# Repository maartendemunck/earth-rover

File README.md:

# Earth Rover

This repository contains the documentation, designs, circuit diagrams, PCB
layouts and firmware of my earth rover (RC Volvo C202) project.

## Electronics

The `electronics` subdirectory contains the circuit diagrams and PCB layouts for
the different components, created with KiCad:

- `human-machine-interface`: main human machine interface (HMI) PCB
- `joystick`: joystick breakout boards for the human machine interface
- `vehicle-control-unit`: main vehicle control unit (VCU) PCB
- `position-encoder`: position encoder for the main driveshaft
- `panel`: panel for fabrication of the PCBs
- `kicad-libraries`: libraries with schematic symbols and component footprints

## Software

The `software/remote-control` subdirectory contains the firmware for a manual
remote control:

- `human-machine-interface`: PlatformIO project for the Teensy 3.2-based human
   machine interface
- `human-machine-interface-display`: Nextion project for the Nextion Enhanced
   NX4827K043 HMI touch display
- `vehicle-control-unit`: PlatformIO project for the Teensy 3.2-based vehicle
   control unit

## License

The earth rover hardware, software and accompanying documentation are released
under the [3-Clause BSD License](https://opensource.org/license/bsd-3-clause/).

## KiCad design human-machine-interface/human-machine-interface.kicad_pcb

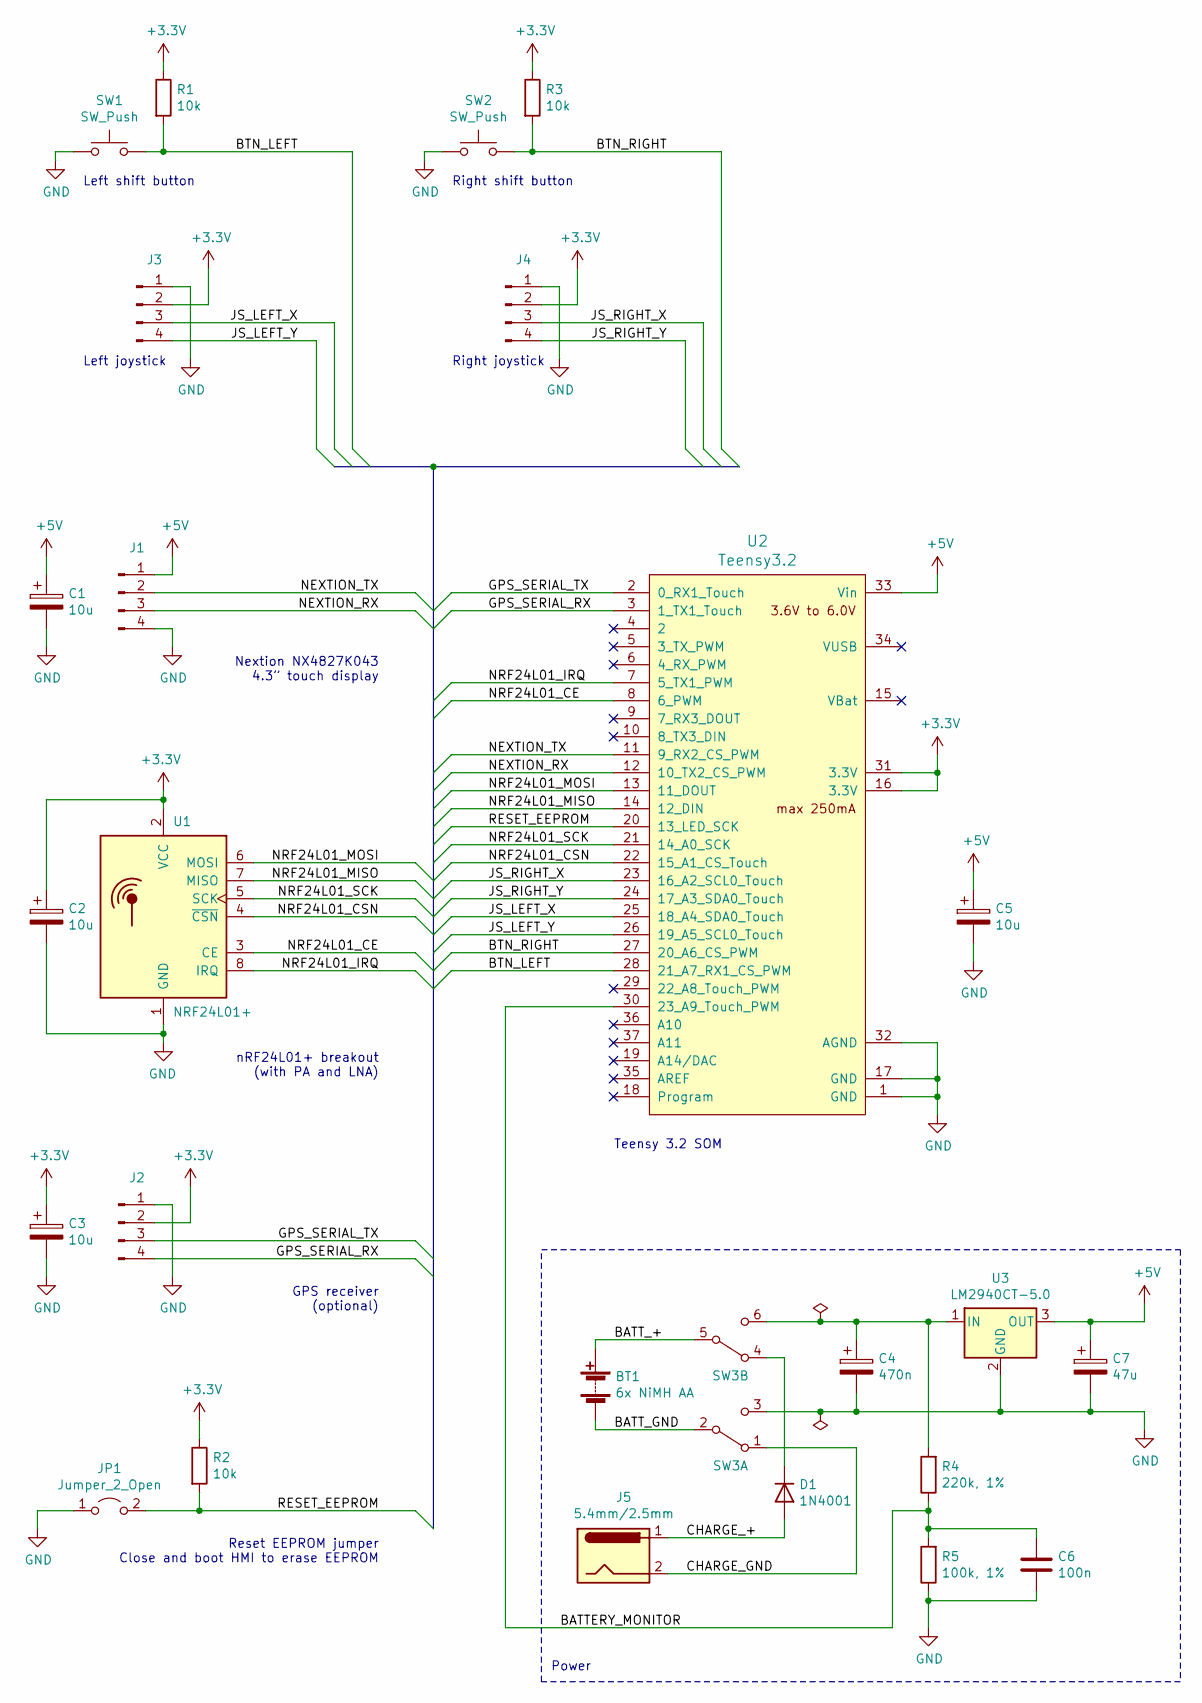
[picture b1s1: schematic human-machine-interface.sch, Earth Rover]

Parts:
BT1: 6x NiMH AA; PinHeader_1x02_P2.54mm_Vertical
C1, C2, C3, C5: 10u; CP_Radial_D5.0mm_P2.50mm
C4: 470n; C_Rect_L10.0mm_W5.0mm_P5.00mm_P7.50mm
C6: 100n; C_Rect_L10.0mm_W5.0mm_P5.00mm_P7.50mm
C7: 47u; CP_Radial_D5.0mm_P2.50mm
D1: 1N4001; D_DO-41_SOD81_P10.16mm_Horizontal
J1, J2, J3, J4: Conn_01x04_Male; PinHeader_1x04_P2.54mm_Vertical
J5: 5.4mm/2.5mm; PinHeader_1x02_P2.54mm_Vertical
JP1: Jumper_2_Open; PinHeader_1x02_P2.54mm_Vertical
R1, R2, R3: 10k; R_Axial_DIN0207_L6.3mm_D2.5mm_P10.16mm_Horizontal
R4: 220k, 1%; R_Axial_DIN0207_L6.3mm_D2.5mm_P10.16mm_Horizontal
R5: 100k, 1%; R_Axial_DIN0207_L6.3mm_D2.5mm_P10.16mm_Horizontal
SW1, SW2: SW_Push; PinHeader_1x02_P2.54mm_Vertical
SW3: SW_DPDT_x2; PinHeader_2x03_P2.54mm_Vertical_Switch_DPDT
U1: NRF24L01+; nRF24L01_Breakout_LargerHoles
U2: Teensy3.2; Teensy_3.2
U3: LM2940CT-5.0; TO-220-3_Vertical

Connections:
+3V3: C2.1, C3.1, J2.2, J3.2, J4.2, R1.1, R2.1, R3.1, U1.2 (VCC), U2.16 (3.3V), U2.31 (3.3V)
+5V: C1.1, C5.1, C7.1, J1.1, U2.33 (Vin), U3.3 (OUT)
/BATTERY_MONITOR: C6.1, R4.1, R5.2, U2.30 (23_A9_Touch_PWM)
/BATT_+: BT1.1 (+), SW3.5 (B)
/BATT_GND: BT1.2 (-), SW3.2 (B)
/BTN_LEFT: R1.2, SW1.2, U2.28 (21_A7_RX1_CS_PWM)
/BTN_RIGHT: R3.2, SW2.2, U2.27 (20_A6_CS_PWM)
/CHARGE_+: D1.2 (A), J5.1
/CHARGE_GND: J5.2, SW3.1 (A)
/GPS_SERIAL_RX: J2.4, U2.3 (1_TX1_Touch)
/GPS_SERIAL_TX: J2.3, U2.2 (0_RX1_Touch)
/JS_LEFT_X: J3.3, U2.25 (18_A4_SDA0_Touch)
/JS_LEFT_Y: J3.4, U2.26 (19_A5_SCL0_Touch)
/JS_RIGHT_X: J4.3, U2.23 (16_A2_SCL0_Touch)
/JS_RIGHT_Y: J4.4, U2.24 (17_A3_SDA0_Touch)
/NEXTION_RX: J1.3, U2.12 (10_TX2_CS_PWM)
/NEXTION_TX: J1.2, U2.11 (9_RX2_CS_PWM)
/NRF24L01_CE: U1.3 (CE), U2.8 (6_PWM)
/NRF24L01_CSN: U1.4 (~CSN), U2.22 (15_A1_CS_Touch)
/NRF24L01_IRQ: U1.8 (IRQ), U2.7 (5_TX1_PWM)
/NRF24L01_MISO: U1.7 (MISO), U2.14 (12_DIN)
/NRF24L01_MOSI: U1.6 (MOSI), U2.13 (11_DOUT)
/NRF24L01_SCK: U1.5 (SCK), U2.21 (14_A0_SCK)
/RESET_EEPROM: JP1.2 (B), R2.2, U2.20 (13_LED_SCK)
GND: C1.2, C2.2, C3.2, C4.2, C5.2, C6.2, C7.2, J1.4, J2.1, J3.1, J4.1, JP1.1 (A), R5.1, SW1.1, SW2.1, SW3.3 (C), U1.1 (GND), U2.1 (GND), U2.17 (GND), U2.32 (AGND), U3.2 (GND)
unnamed: C4.1, R4.2, SW3.6 (C), U3.1 (IN)
unnamed: D1.1 (K), SW3.4 (A)

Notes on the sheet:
GPS receiver (optional)
Right joystick
Reset EEPROM jumper Close and boot HMI to erase EEPROM
Power
nRF24L01+ breakout (with PA and LNA)
Left shift button
Left joystick
Right shift button
Nextion NX4827K043 4.3” touch display
Teensy 3.2 SOM

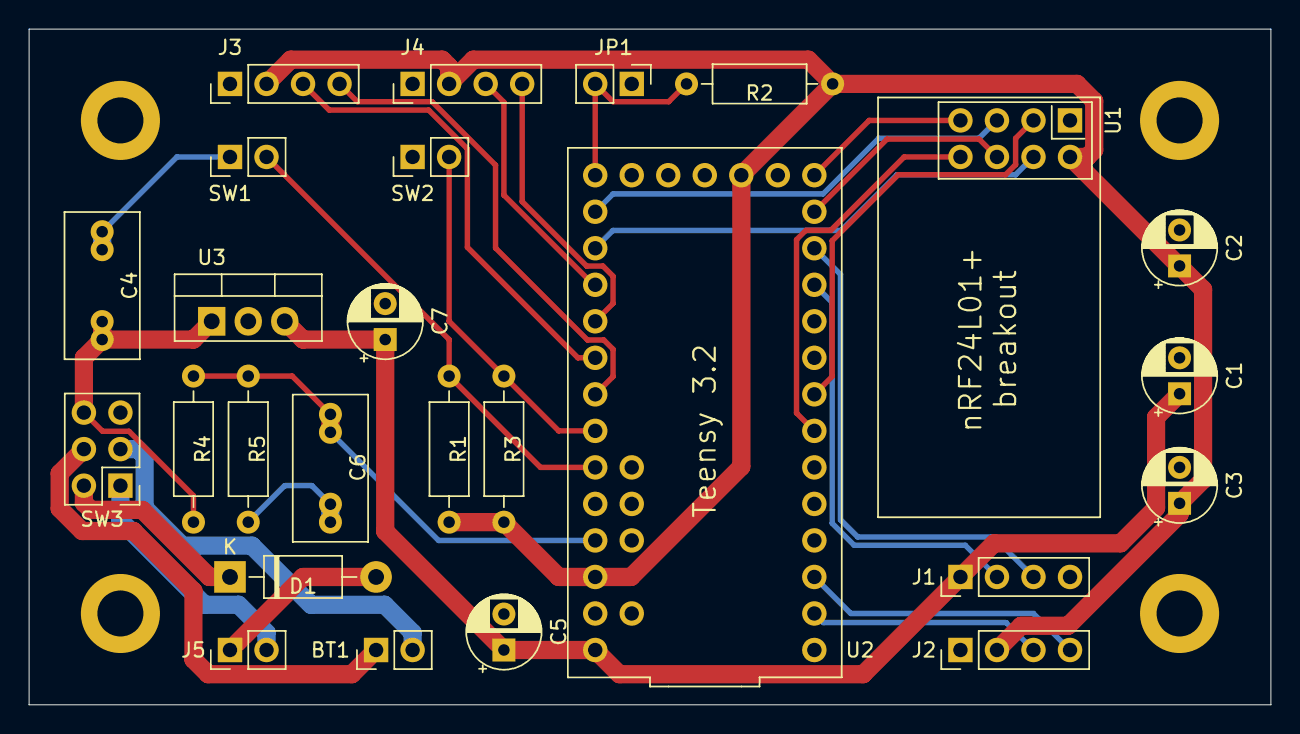
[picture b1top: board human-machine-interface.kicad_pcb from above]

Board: 2 copper layers, 86.4 x 47.0 mm, 26 parts (0 on the bottom side), 27 nets.

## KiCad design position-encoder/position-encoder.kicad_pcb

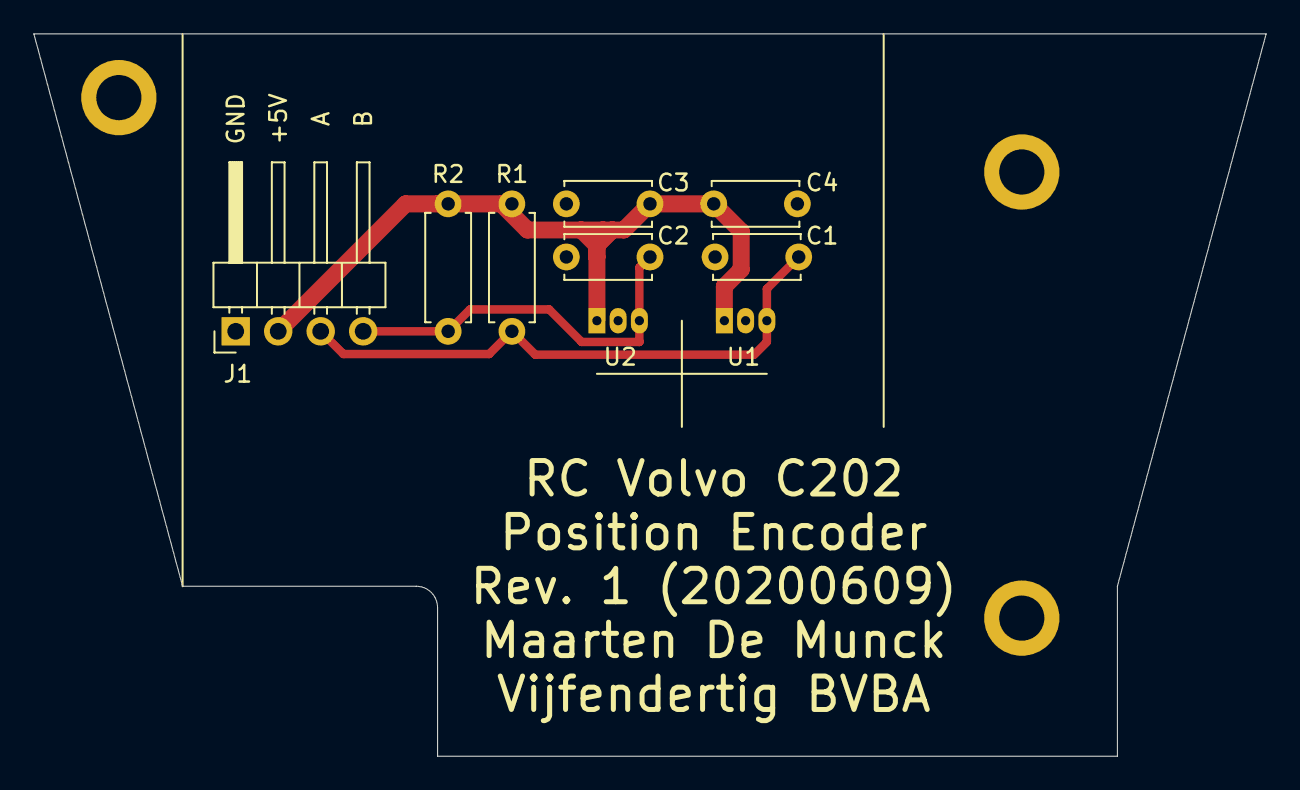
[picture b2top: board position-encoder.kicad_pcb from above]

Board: 2 copper layers, 73.7 x 43.2 mm, 9 parts (0 on the bottom side), 4 nets.

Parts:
C1, C2, C3, C4: 4.7nF; C_Disc_D5.0mm_W2.5mm_P5.00mm
J1: Conn_01x04_Male; PinHeader_1x04_P2.54mm_Horizontal
R1, R2: 10kΩ; R_Axial_DIN0207_L6.3mm_D2.5mm_P7.62mm_Horizontal
U1, U2: TLE4905L; PG-SSO-3-2_W2.54mm_Horizontal_Down

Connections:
+5V: C3.1, C4.1, J1.2, R1.1, R2.1, U1.1, U2.1
GND: C1.2, C2.2, C3.2, C4.2, J1.1, U1.2, U2.2
unnamed: C1.1, J1.3, R1.2, U1.3
unnamed: C2.1, J1.4, R2.2, U2.3

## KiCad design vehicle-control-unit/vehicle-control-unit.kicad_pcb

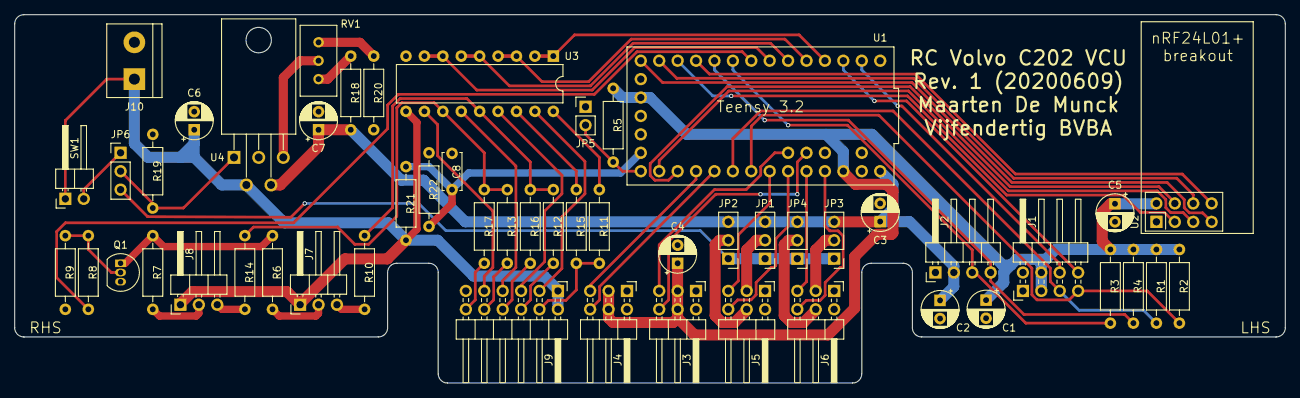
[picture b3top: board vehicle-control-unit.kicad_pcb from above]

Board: 2 copper layers, 175.3 x 50.8 mm, 53 parts (0 on the bottom side), 60 nets.

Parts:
C1, C2, C3, C4, C5, C6: 10u; CP_Radial_D5.0mm_P2.50mm
C7: 22u; CP_Radial_D5.0mm_P2.50mm
C8: 100n; C_Disc_D5.0mm_W2.5mm_P5.00mm
J1: Conn_02x04_Male_UnitPerRow; PinHeader_2x04_P2.54mm_Horizontal
J2: Conn_01x04_Male; PinHeader_1x04_P2.54mm_Horizontal
J3, J4, J5, J6: Conn_02x03_Male; PinHeader_2x03_P2.54mm_Horizontal
J7, J8: Conn_01x03_Male; PinHeader_1x03_P2.54mm_Horizontal
J9: Conn_02x06_Male_UnitPerRow; PinHeader_2x06_P2.54mm_Horizontal
J10: Connector:Screw_Terminal_01x02; TerminalBlock_bornier-2_P5.08mm
JP1, JP2, JP3, JP4, JP6: Jumper_3_Bridged12; PinHeader_1x03_P2.54mm_Vertical
JP5: Jumper_2_Open; PinHeader_1x02_P2.54mm_Vertical
Q1: BC517; TO-92_Inline
R1, R2, R3, R4, R5, R8, R19: 10k; R_Axial_DIN0207_L6.3mm_D2.5mm_P10.16mm_Horizontal
R6, R7: 10E; R_Axial_DIN0207_L6.3mm_D2.5mm_P10.16mm_Horizontal
R9: 100k; R_Axial_DIN0207_L6.3mm_D2.5mm_P10.16mm_Horizontal
R10, R14, R16, R17: 330E; R_Axial_DIN0207_L6.3mm_D2.5mm_P10.16mm_Horizontal
R11: 470E; R_Axial_DIN0207_L6.3mm_D2.5mm_P10.16mm_Horizontal
R12, R13: 180E; R_Axial_DIN0207_L6.3mm_D2.5mm_P10.16mm_Horizontal
R15: 82E; R_Axial_DIN0207_L6.3mm_D2.5mm_P10.16mm_Horizontal
R18: 820E; R_Axial_DIN0207_L6.3mm_D2.5mm_P10.16mm_Horizontal
R20: 240E; R_Axial_DIN0207_L6.3mm_D2.5mm_P10.16mm_Horizontal
R21: 270k, 1%; R_Axial_DIN0207_L6.3mm_D2.5mm_P10.16mm_Horizontal
R22: 100k, 1%; R_Axial_DIN0207_L6.3mm_D2.5mm_P10.16mm_Horizontal
RV1: 100E; Potentiometer_Bourns_3296W_Vertical
SW1: SW_SPST; PinHeader_1x02_P2.54mm_Horizontal
U1: Teensy3.2; Teensy_3.2
U2: NRF24L01+ breakout; nRF24L01_Breakout_LargerHoles
U3: ULN2803A; DIP-18_W7.62mm
U4: MIC29502WT; TO-220-5_P3.4x3.8mm_StaggerEven_Lead7.13mm_TabDown

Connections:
+3V3: C1.1, C4.1, C5.1, J1.3, J1.4, J3.3, J3.4, J4.3, J4.4, R1.1, R2.1, R3.1, R4.1, R5.1, U1.16, U1.31, U2.2
+5V: C2.1, C3.1, C7.1, J2.2, JP1.3, JP2.3, JP3.3, JP4.3, R18.1, U1.33, U4.4
+BATT: C6.1, J7.1, J8.1, J9.1, J9.2, J10.1, R21.1, SW1.1, U3.10, U4.2
/BATTERY_MONITOR: C8.1, R21.2, R22.1, U1.19
/BEC: JP1.1, JP2.1, JP3.1, JP4.1, JP6.3
/ENCODER_A: J2.3, R3.2, U1.9
/ENCODER_B: J2.4, R4.2, U1.10
/GEARBOX: J6.5, U1.29
/GPS_SERIAL_RX: J1.8, U1.3
/GPS_SERIAL_TX: J1.6, U1.2
/HEADLAMPS: R8.2, U1.8
/IMU_I2C_SCL: J1.7, R2.2, U1.26
/IMU_I2C_SDA: J1.5, R1.2, U1.25
/LEFT_TURN_SIGNALS: U1.6, U3.5, U3.6
/NRF24L01_CE: U1.12, U2.3
/NRF24L01_CSN: U1.22, U2.4
/NRF24L01_IRQ: U1.11, U2.8
/NRF24L01_MISO: U1.14, U2.7
/NRF24L01_MOSI: U1.13, U2.6
/NRF24L01_SCK: U1.21, U2.5
/POSITION_LAMPS: U1.4, U3.1, U3.2
/RESET_EEPROM: JP5.2, R5.2, U1.20
/RIGHT_TURN_SIGNALS: U1.7, U3.7, U3.8
/SENSOR_1: J3.6, U1.36
/SENSOR_2: J3.5, U1.37
/SENSOR_3: J4.6, U1.24
/SENSOR_4: J4.5, U1.23
/STEERING: J5.5, U1.27
/STOP_LAMPS: U1.5, U3.3, U3.4
/THROTTLE: J5.6, U1.28
/WINCH: J6.6, U1.30
GND: C1.2, C2.2, C3.2, C4.2, C5.2, C6.2, C7.2, C8.2, J1.1, J1.2, J2.1, J3.1, J3.2, J4.1, J4.2, J5.1, J5.2, J6.1, J6.2, J9.11, J10.2, JP5.1, Q1.3, R9.2, R19.2, R20.2, R22.2, U1.1, U1.17, U1.32, U2.1, U3.9, U4.3
unnamed: J5.3, JP1.2
unnamed: J5.4, JP2.2
unnamed: J6.3, JP3.2
unnamed: J6.4, JP4.2
unnamed: J7.2, R6.1
unnamed: J7.3, R10.1
unnamed: J8.2, R7.1
unnamed: J8.3, R14.1
unnamed: J9.3, U3.17
unnamed: J9.4, R11.1, R15.1
unnamed: J9.5, U3.15
unnamed: J9.6, R12.1
unnamed: J9.7, U3.13
unnamed: J9.8, R16.1
unnamed: J9.9, U3.11
unnamed: J9.10, R13.1
unnamed: J9.12, R17.1
unnamed: JP6.1, SW1.2
unnamed: JP6.2, R19.1, U4.1
unnamed: Q1.1, R6.2, R7.2
unnamed: Q1.2, R8.1, R9.1
unnamed: R10.2, R12.2, R16.2, U3.14
unnamed: R11.2, U3.18
unnamed: R13.2, R14.2, R17.2, U3.12
unnamed: R15.2, U3.16
unnamed: R18.2, RV1.1
unnamed: R20.1, RV1.3
unnamed: RV1.2, U4.5

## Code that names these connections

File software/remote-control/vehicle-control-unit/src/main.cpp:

// Copyright 2019-2023 Vijfendertig BV.
//
// This file is part of the Earth Rover project, which is licensed under the 3-Clause BSD License.
// See the file LICENSE.md or go to https://opensource.org/license/bsd-3-clause/ for full license
// details.

#include <Arduino.h>
#include <i2c_t3.h>

#include "adafruit-bno055-wrapper.hpp"
#include "lighting.hpp"
#include "neogps-wrapper.hpp"
#include "position-encoder.hpp"
#include "powertrain.hpp"
#include "radio-configuration.hpp"
#include "steering-servo.hpp"
#include "vcu-communicator.hpp"
#include "vcu.hpp"

// #define SERIAL_DEBUG

constexpr uint8_t spi_sck_pin = 14u;  // Use the default SCK pin 13 as status LED.

auto makeVcu() {
    constexpr uint16_t config_eeprom_block_offset = 0u;
    constexpr uint16_t config_eeprom_block_size = 2048u;
    constexpr uint8_t steering_servo_pin = 20u;
    constexpr uint8_t esc_pin = 21u;
    constexpr uint8_t gearbox_servo_pin = 22u;
    constexpr uint8_t head_lamp_pin = 6u;
    constexpr uint8_t tail_lamp_pin = 2u;
    constexpr uint8_t stop_lamp_pin = 3u;
    constexpr uint8_t turn_signal_left_pin = 4u;
    constexpr uint8_t turn_signal_right_pin = 5u;
    constexpr uint8_t hall_sensor_a_pin = 7u;
    constexpr uint8_t hall_sensor_b_pin = 8u;
    constexpr uint16_t pulses_per_km = 23000u;
    constexpr auto &imu_i2c = Wire;
    constexpr uint8_t imu_i2c_scl_pin = 19u;
    constexpr uint8_t imu_i2c_sda_pin = 18u;
    constexpr auto &gps_serial = Serial1;
    constexpr uint8_t gps_serial_rx_pin = 0u;
    constexpr uint8_t gps_serial_tx_pin = 1u;
    earth_rover::SteeringServo steering_servo{steering_servo_pin};
    earth_rover::Powertrain powertrain{esc_pin, gearbox_servo_pin};
    earth_rover::Lighting lighting{head_lamp_pin, tail_lamp_pin, stop_lamp_pin,
                                   turn_signal_right_pin, turn_signal_left_pin};
    earth_rover::PositionEncoder<hall_sensor_a_pin, hall_sensor_b_pin> position_encoder{
        pulses_per_km, 0u, 0u};
    earth_rover::AdafruitBNO055Wrapper<decltype(imu_i2c)> imu{imu_i2c, imu_i2c_scl_pin,
                                                              imu_i2c_sda_pin};
    earth_rover::NeoGpsWrapper<decltype(gps_serial)> gps{gps_serial, gps_serial_rx_pin,
                                                         gps_serial_tx_pin};
    earth_rover::RadioConfig radio_config;
    earth_rover::Vcu<decltype(steering_servo), decltype(powertrain), decltype(lighting),
                     decltype(position_encoder), decltype(imu), decltype(gps),
                     decltype(radio_config)>
        vcu{config_eeprom_block_offset,
            config_eeprom_block_size,
            std::move(steering_servo),
            std::move(powertrain),
            std::move(lighting),
            std::move(position_encoder),
            std::move(imu),
            std::move(gps),
            std::move(radio_config)};
    return vcu;
}

auto vcu = makeVcu();

auto makeCommunicator(decltype(vcu) &vcu) {
    constexpr uint8_t rf24_ce_pin = 10u;
    constexpr uint8_t rf24_csn_pin = 15u;
    earth_rover::VcuCommunicator<decltype(vcu)> communicator{rf24_ce_pin, rf24_csn_pin, vcu};
    return communicator;
}

auto communicator = makeCommunicator(vcu);
// auto configuration_manager = earth_rover::makeVcuConfigManager(
//     steering_servo, powertrain, position_encoder, imu, radio_config, 0u, 2048u);

void setup() {
    pinMode(LED_BUILTIN, OUTPUT);
    digitalWrite(LED_BUILTIN, 1);
// Setup debug console (if enabled).
#ifdef SERIAL_DEBUG
    Serial.begin(9600);
    while(!Serial) {
        ;
    }
#endif
    SPI.setSCK(spi_sck_pin);
    // configuration_manager.setup();
    vcu.setup();
    communicator.setup();
    digitalWrite(LED_BUILTIN, 0);
}

void loop() {
    communicator.spinOnce();
    vcu.spinOnce();
    // configuration_manager.spinOnce();
}

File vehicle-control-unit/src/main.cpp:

//! Earth Rover VCU (vehicle control unit) sketch for a Teensy 3.2.
/*!
 *  \ingroup VCU
 *  \file
 *  \author Maarten De Munck <maarten@vijfendertig.be>
 */


#include <Arduino.h>
#include <i2c_t3.h>

#include "steering-servo.hpp"
#include "powertrain.hpp"
#include "lighting.hpp"
#include "position-encoder.hpp"
#include "adafruit-bno055-wrapper.hpp"
#include "neogps-wrapper.hpp"
#include "radio-configuration.hpp"
#include "vcu.hpp"
#include "vcu-communicator.hpp"
#include "vcu-configuration-manager.hpp"


// #define SERIAL_DEBUG
// #define RESET_EEPROM_MEMORY


/*
 *  Pin assignments.
 */

constexpr uint8_t steering_servo_pin = 20u;    //!< I/O pin used to control the steering servo.
constexpr uint8_t esc_pin = 21u;               //!< I/O pin used to control the electronic speed controller (ESC).
constexpr uint8_t gearbox_servo_pin = 22u;     //!< I/O pin used to control the gearbox servo.
constexpr uint8_t head_lamp_pin = 6u;          //!< I/O pin used to control the head lamps.
constexpr uint8_t tail_lamp_pin = 2u;          //!< I/O pin used to control the tail lamps.
constexpr uint8_t stop_lamp_pin = 3u;          //!< I/O pin used to control the stop lamps.
constexpr uint8_t turn_signal_left_pin = 4u;   //!< I/O pin used to control the left turn signal.
constexpr uint8_t turn_signal_right_pin = 5u;  //!< I/O pin used to control the right turn signal.

constexpr i2c_t3 & imu_i2c = Wire;             //!< I²C interface used by the BNO055 IMU.
constexpr uint8_t imu_i2c_scl_pin = 19u;       //!< I/O pin used for the I²C interface's SCL signal.
constexpr uint8_t imu_i2c_sda_pin = 18u;       //!< I/O pin used for the I²C interface's SDA signal.

constexpr uint8_t spi_sck_pin = 14u;           //!< I/O pin used for the SPI's SCK signal.
constexpr uint8_t rf24_ce_pin = 10u;           //!< I/O pin used for the nRF24L01+'s CE signal.
constexpr uint8_t rf24_csn_pin = 15u;          //!< I/O pin used for the nRF24L01+'s CSN signal.


/*
 *  Vehicle systems.
 */

//! Steering servo device driver.
earth_rover_vcu::SteeringServo steering_servo {steering_servo_pin};
//! Powertrain device driver.
earth_rover_vcu::Powertrain powertrain {esc_pin, gearbox_servo_pin};
//! Automotive lighting device driver.
earth_rover_vcu::Lighting lighting {
  head_lamp_pin, tail_lamp_pin, stop_lamp_pin, turn_signal_right_pin, turn_signal_left_pin};
//! Position encoder device driver.
earth_rover_vcu::PositionEncoder<7u, 8u> position_encoder {23000u, 0u, 0u};
//! IMU device driver.
earth_rover_vcu::AdafruitBNO055Wrapper<i2c_t3> imu {imu_i2c, imu_i2c_scl_pin, imu_i2c_sda_pin};
//! GPS device driver.
earth_rover_vcu::NeoGpsWrapper<HardwareSerial> gps {Serial1, 0, 1};
//! HMI and VCU radio (nRF24L01+) configuration.
earth_rover_vcu::RadioConfiguration radio_configuration;

//! VCU subsystem abstraction.
auto vcu = earth_rover_vcu::makeVcu(
  steering_servo, powertrain, lighting, position_encoder, imu, gps, radio_configuration);
//! VCU communicator.
earth_rover_vcu::VcuCommunicator<decltype(vcu)> communicator {rf24_ce_pin, rf24_csn_pin, vcu};
//! VCU configuration.
auto configuration_manager = earth_rover_vcu::makeVcuConfigurationManager(
  steering_servo, powertrain, position_encoder, imu, radio_configuration, 0u, 2048u);


/*
 *   Sketch.
 */

//! Initialize the VCU.
void setup()
{
  // Initialisation started, switch on built in LED.
  pinMode(LED_BUILTIN, OUTPUT);
  digitalWrite(LED_BUILTIN, 1);
  // Setup debug console (if enabled).
  #ifdef SERIAL_DEBUG
    Serial.begin(9600);
    while(!Serial)
    {
      ;
    }
  #endif
  // Reset EEPROM memory (if enabled).
  #ifdef RESET_EEPROM_MEMORY
    uint8_t imu_calibration[32] =
      {0x02, 0xff, 0x02, 0x00, 0x00, 0x00, 0x09, 0x00, 0x93, 0xff, 0x05, 0x00, 0xe0, 0x02, 0x78, 0x02,
       0x88, 0x01, 0x00, 0x00, 0x00, 0x00, 0x00, 0x00, 0xe8, 0x03, 0x10, 0x03, 0xff, 0xff, 0x8b, 0x4a};
    for(uint16_t index = 32; index < 64; ++ index)
    {
      EEPROM.update(index, imu_calibration[index - 32]);
    }
    for(uint16_t index = 64; index < 2048; ++ index)
    {
      EEPROM.update(index, 0xffu);
    }
    Serial.println("EEPROM memory cleared.");
    while(true)
    {
      digitalWrite(LED_BUILTIN, 0);
      delay(250);
      digitalWrite(LED_BUILTIN, 1);
      delay(250);
    }
  #endif
  // Configure SPI.
  SPI.setSCK(spi_sck_pin);  // Use the default SCK pin 13 as status LED.
  // Read the configuration stored in EEPROM.
  configuration_manager.setup();
  // Setup the VCU.
  vcu.setup();
  // Configure nRF24L01+ communication module.
  communicator.setup();
  // Initialisation finished, switch off built in LED.
  digitalWrite(LED_BUILTIN, 0);
}

//! Spinning loop.
void loop()
{
  communicator.spinOnce();
  vcu.spinOnce();
  configuration_manager.spinOnce();
}

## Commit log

2019-06-19 Start design documentation
2019-06-22 Documentation updates and Makefile
    Add the pin assignment on the HMI's Teensy 3.2 microcontroller.
    Add a Makefile for the documentation (calling lyx).
2019-07-01 Add PlatformIO projects for HMI and VCU
    Add PlatformIO projects for the remote control's human machine interface
    firmware and vehicle control unit firmware.
2019-07-01 Add remote control submodule
2019-07-02 Add github.com/nRF24/RF24 library
2019-07-02 Use updated remote control submodule
2019-07-08 Transmit 2 analog values via nRF24L01+
    Implement a prototype transmitting two analog values over the nRF24L01+
    transceivers.
2019-07-09 Clean up HMI prototype code
2019-07-09 Clean up VCU prototype code
2019-07-09 Add steering and throttle servo control to VCU
2019-07-10 Implement timeout callback in VCU
2019-08-16 Create Nextion HMI interface
    Create HMI application for Nextion NX4827K043, including custom
    communication on touch events.
2019-08-16 Create config objects and init settings pages
    Create configuration objects for the HMI and VCU configuration
    parameters and send the initial configuration to the Nextion display.
2019-08-20 Implement communication of drive commands
    HMI side implemented using configuration and state objects.
    VCU side still implemented ad-hoc.
2019-08-22 Add communication between HMI and VCU to documentation
2019-08-22 Add Nextion status messages to documentation
2019-08-30 Add software block diagram to documentation
2019-09-07 Implement FHSS
2019-09-08 Fix bugs in FHSS
    Fix bug in FHSS receiver code.
    Replace channel list by something that works reliable with my Velleman
    nRF24L01+ modules.
2019-09-09 Update communication and shut off turn signals
    Update communication protocol to 72 bits (9 bytes) payload (8 command
    bits and 64 data bits).
    Automatically shut off turn signals after a turn.
2019-09-10 Add automotive lighting to VCU
2019-09-10 Remove debug output to USB serial port
2019-09-12 Fix servo initialization and only shift while driving
    Fix servo initialization. The steering servo requires an additional
    setPosition call (on top of the call in the setup function) to prevent
    fully steering to the left until the synchronization with the
    transmitter is established.
    Only shift while driving to ensure quick engagement, lowering the stress
    on the gearbox servo.
2019-09-16 Update software block diagram
2019-09-16 Reorganize VCU code
2019-09-18 Add Adafruit Bosch BNO055 sensor
2019-09-19 Update documentation
2019-09-19 Add orientation request, response and visualization
2019-09-22 Add GPS sensor and location and altitude request and response
2019-09-23 Invalidate old location and altitude data
2019-09-23 Improve sensor data handling
2019-09-23 Improve VCU code
2019-09-23 Fix bugs
2019-09-23 Fix bugs in Nextion GUI code
2019-10-03 Add distance and speed encoder
2019-10-04 Embed GPS functionality in a separate class
    Embed the GPS functionality in a separate NeoGPS wrapper class, moving
    the details (the serial device and its configuration and initialization
    and the data processing) outside the Vcu class.
2019-10-04 Add Doxygen documentation
2019-10-04 Refactor code and add documentation
2019-10-04 Use relative link in .gitmodules
2019-10-06 Add wrapper for the BNO055 IMU and add documentation
    Add a device-independent-interface-wrapper for the Adafruit BNO055 IMU.
    Continue documenting all code.
2019-10-07 Fix potential bug and add documentation
    Fix potential bug (potential incompatibility with non-Teense boards) in
    position encoder.
    Add documentation.
2019-10-07 Fix bug and add documentation
    Fix bug in servo pulse width limitations.
    Add documentation.
2019-10-08 Add documentation
2019-10-08 Add GitLab CI script
2019-10-09 Refactor and add documentation
2019-10-11 Refactoring HMI
2019-10-12 Refactoring HMI (documentation still incomplete)
2019-10-14 Allow enabling and disabling the settings pages
2019-10-15 Refactor steering servo and powertrain configuration
2019-10-16 Refactor configuration
2019-10-16 Simplify subsystem state objects
2019-10-16 Make VCU answer configuration requests
2019-10-16 Fix default pulse widths
2019-10-16 Request and receive steering configuration
    Request steering servo configuration and process received answer.
    Enable configuration pages when configuration in HMI is complete
    (currently when the steering configuration is received). This also
    required a change in the Nextion HMI code (variable name too long
    apparently).
2019-10-17 Request and receive throttle and gearbox configuration
2019-10-17 Fix missed first message from Nextion HMI display
2019-10-17 Request and receive radio configuration
2019-10-18 Send configuration changes in HMI to VCU
2019-10-18 Apply steering servo and powertrain configuration
    Apply steering servo and powertrain configuration received from HMI.
    Simplified gearbox servo configuration (assume two speed with neutral
    except in the communication protocol itself).
2019-10-19 Use configured input channels
2019-10-19 Add missing documentation
2019-10-20 Apply radio PA power level configuration
2019-10-26 Save odometer value to EEPROM and restore it on boot
2019-10-27 Fix bug displaying pitch and roll values < -45 degrees
2019-10-27 Save IMU calibration to EEPROM and restore it on boot
2019-10-28 Save steering configuration to EEPROM and restore it on boot
2019-10-29 Save radio configuration to EEPROM and restore it on boot
2019-10-29 Save powertrain configuration to EEPROM and restore it on boot and fix bugs
2019-10-29 Fix bug
2019-10-29 Add IMU calibration to EEPROM reset code
2019-10-29 Add remote control (initial operational version)
2019-10-30 Fix IMU orientation (yaw)
2019-11-11 Add circuit diagram for position encoder
2019-11-11 Add repo with circuit diagrams and PCB layouts as a submodule
2019-11-13 Add PCB for position encoder
2019-11-14 Update PCB
2019-11-14 Add fp-lib-table file
2019-11-14 Improve PCB
2019-11-21 Add custom KiCad page layout
2019-11-22 Limit field lengths in page layout
2019-11-24 Add HMI schematic
2019-11-25 Improve layout of HMI schematic
2019-11-25 Add (optional) GPS receiver to HMI schematic
2019-11-29 Add part of VCU schematic
2019-11-30 Finish VCU schematic
2019-12-01 Improve layouts and add capacitors
2019-12-06 Add Alps Alpine ThumbPointer RKJXK122000D footprint
2019-12-12 Move the HMI's thumbsticks to separate boards
2019-12-14 Update power supply of HMI
2019-12-20 Review schematics
2019-12-21 Correct resistor value for battery monitor
2019-12-21 Add custom symbol library configuration
2019-12-23 Add PCB for joystick breakout board
2020-01-31 Add pulldown resistor on MIC29502WT's EN input
2020-02-23 Fix some errors in the VCU hardware
2020-02-23 Add diode to HMI's charge port
2020-02-23 Make lighting software compatible with hardware design
2020-02-23 Add updated Visual Studio Code configuration files
2020-02-23 Add schematics and software as used in prototype
2020-04-25 Wire all turn signal LEDs in parallel
2020-04-27 Fix missing pinMode in destructor
2020-04-27 Fix typo in comment
2020-04-27 Configure Clang-Format and format C++ source files
2020-04-27 Update VSCode workspace settings to match CLang-Format settings
2020-04-27 Add missing #include
2020-05-05 Add PlatformIO/Unity unit tests
2020-05-05 Fix CI configuration
2020-05-05 Add unit tests
2020-06-01 Assign footprints
2020-06-01 Draw PCB outline
2020-06-08 Route PCB
2020-06-08 Clean up routing
2020-06-08 Finish VCU PCB
2020-06-09 Update PCB of position encoder
2020-06-09 Improve ground plane of VCU PCB
2020-06-09 Change mounting hole diameter to 2.54mm
2020-06-11 Update joystick breakout board
2020-06-12 Route HMI PCB
2020-06-12 Finish HMI PCB
2020-06-12 Use proper mounting holes
2020-06-12 Add panel
2020-06-17 Update panel according to Eurocircuits' specifications
2020-06-23 Use larger holes for nRF24L01+ breakout board
2020-08-05 Change value of rear turn signal resistors
2023-01-23 Remove old KiCad libraries
2023-01-23 Prepare merging submodules into main repository
2023-01-23 Update README.md file(s)
2023-03-14 Update technical documentation
2023-03-17 Add 3-Clause BSD License
2023-03-17 Improve and refactor HMI (incl Nextion display)
    Implement the configuration of the HMI. The center and extreme positions
    of the sticks can be teached via the menu on the Nextion display. These
    settings are stored in the non-volatile memory (EEPROM) of the HMI
    itself.
    Improve high beam handling. The high beam is automatically switched of
    when the low beam is off, similar to real cars.
2023-03-17 Refactor VCU Teensy firmware
2023-03-17 Use available radio spectrum
2023-03-19 Fix bugs sending and saving the configuation
    Fix bugs in sending the configuration from the HMI to the VCU and saving
    the configuration in the EEPROM of the VCU.
    Handle the transmission as a two speed transmission (low and high, no
    neutral). Initialise the transmission on the average of low and high and
    move to either low or high as soon as the car starts driving. This
    prevents putting too much strain on the transmission servo if the car is
2023-03-19 Fix some potential code issues
2023-03-19 Fix communication error in HMI
